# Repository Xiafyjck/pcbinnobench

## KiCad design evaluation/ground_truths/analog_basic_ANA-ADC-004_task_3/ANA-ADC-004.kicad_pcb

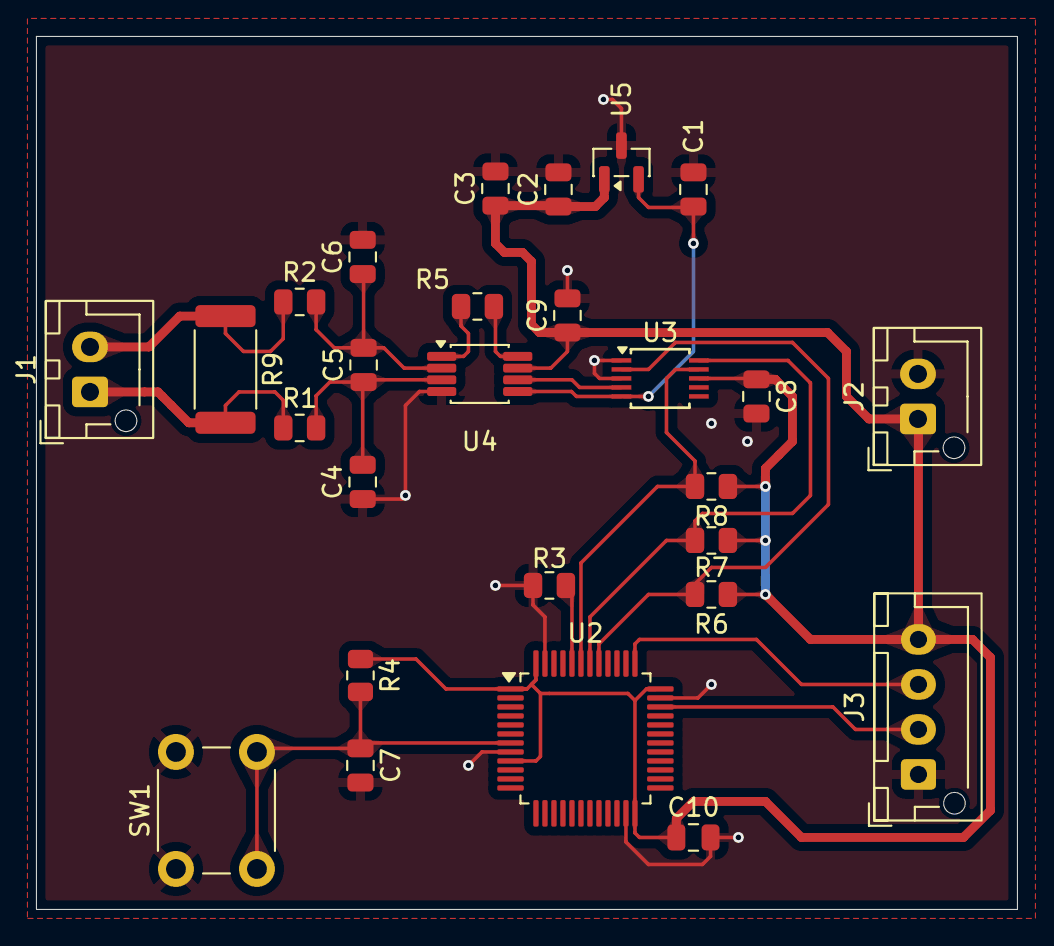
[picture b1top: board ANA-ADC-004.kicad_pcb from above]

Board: 2 copper layers, 54.5 x 48.5 mm, 27 parts (0 on the bottom side), 17 nets.

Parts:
C1: 10uF; C_0805_2012Metric
C2, C8, C9: 0.1uF; C_0805_2012Metric
C3: 1uF; C_0805_2012Metric
C4, C5, C6: 1nF; C_0805_2012Metric
C7, C10: 100nF; C_0805_2012Metric
J1, J2: Conn_01x02_Pin; JST_XH_B2B-XH-AM_1x02_P2.50mm_Vertical
J3: Conn_01x04_Pin; JST_XH_B4B-XH-AM_1x04_P2.50mm_Vertical
R1, R2, R3, R4, R6: 10k; R_0805_2012Metric
R5: 100k; R_0805_2012Metric
R7, R8: 4.7k; R_0805_2012Metric
R9: 10; R_2512_6332Metric
SW1: SW_Push; SW_PUSH_6mm
U2: STM32F103C8Tx; LQFP-48_7x7mm_P0.5mm
U3: ADS1115IDGS; TSSOP-10_3x3mm_P0.5mm
U4: INA333xxDGK; VSSOP-8_3x3mm_P0.65mm
U5: REF3012; SOT-23

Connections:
+3.3V: C2.1, C3.1, C8.1, C9.1, C10.1, J2.1, J3.4, R4.1, R6.1, R7.1, R8.1, U2.1 (VBAT), U2.9 (VDDA), U2.24 (VDD), U2.36 (VDD), U2.48 (VDD), U3.8 (VDD), U4.7 (V+), U5.1 (IN)
/ADC_HIN: J1.1, R1.1, R9.2
/ADC_LIN: J1.2, R2.1, R9.1
/stm32/ADS_ALERT: R6.2, U2.41 (PB5), U3.2 (ALERT/RDY)
/stm32/BOOT0: R3.1, U2.44 (BOOT0)
/stm32/I2C1_SCL: R7.2, U2.42 (PB6), U3.10 (SCL)
/stm32/I2C1_SDA: R8.2, U2.43 (PB7), U3.9 (SDA)
/stm32/NRST: C7.1, R4.2, SW1.2, U2.7 (NRST)
/stm32/swclk: J3.3, U2.37 (PA14)
/stm32/swdio: J3.2, U2.34 (PA13)
/vref: C1.1, U3.5 (AIN1), U4.5 (Ref), U5.2 (OUT)
GND: C1.2, C2.2, C3.2, C4.1, C6.2, C7.2, C8.2, C9.2, C10.2, J2.2, J3.1, R3.2, SW1.1, U2.8 (VSSA), U2.23 (VSS), U2.35 (VSS), U2.47 (VSS), U3.1 (ADDR), U3.3 (GND), U4.4 (V-), U5.3 (GND)
unnamed: R5.1, U4.8 (Rg)
unnamed: R5.2, U4.1 (Rg)
unnamed: U3.4 (AIN0), U4.6
unnamed: C4.2, C5.1, R1.2, U4.3 (+)
unnamed: C5.2, C6.1, R2.2, U4.2 (-)

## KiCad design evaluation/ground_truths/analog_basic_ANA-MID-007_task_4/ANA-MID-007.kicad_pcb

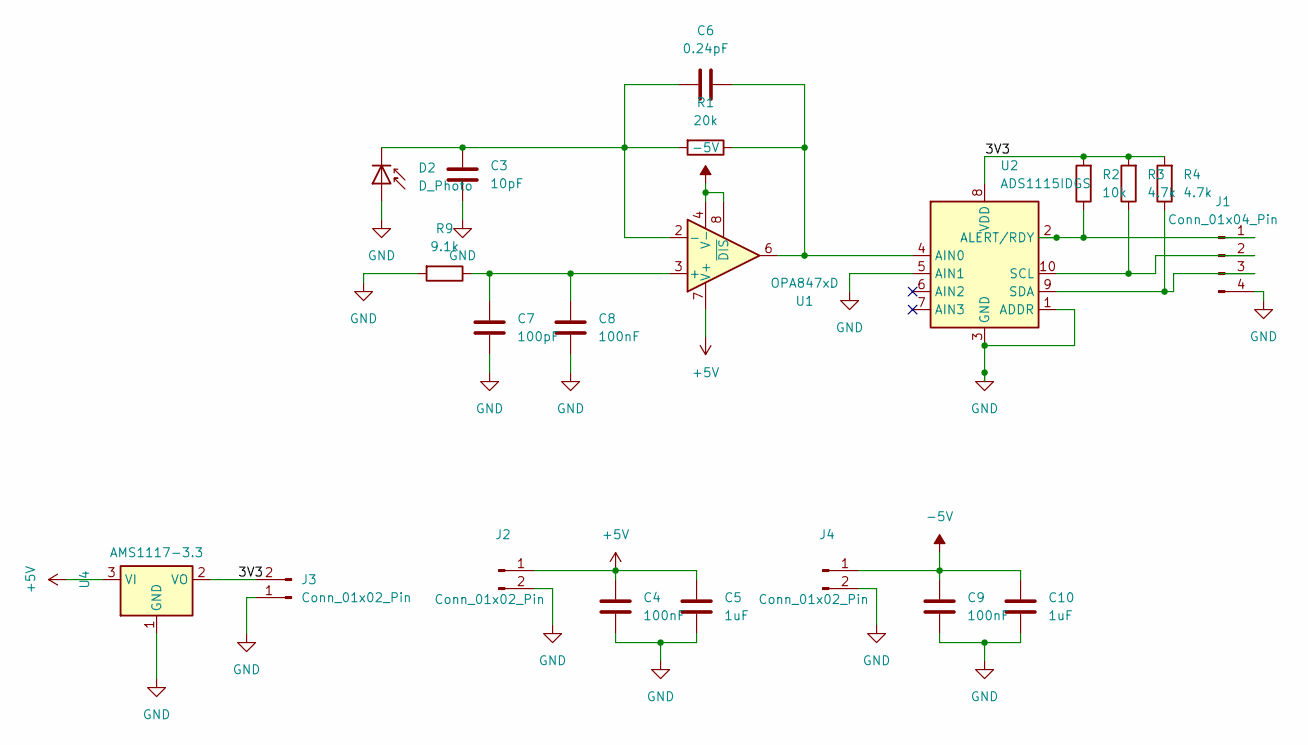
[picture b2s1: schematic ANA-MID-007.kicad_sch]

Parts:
C3: 10pF; C_0805_2012Metric
C4, C8, C9: 100nF; C_0805_2012Metric
C5, C10: 1uF; C_0805_2012Metric
C6: 0.24pF; C_0805_2012Metric
C7: 100pF; C_0805_2012Metric
D2: D_Photo; TO-18-2
J1: Conn_01x04_Pin; PinHeader_1x04_P2.54mm_Horizontal
J2, J3, J4: Conn_01x02_Pin; PinHeader_1x02_P2.54mm_Horizontal
R1: 20k; R_0805_2012Metric
R2: 10k; R_0805_2012Metric
R3, R4: 4.7k; R_0805_2012Metric
R9: 9.1k; R_0805_2012Metric
U1: OPA847xD; SOIC-8_3.9x4.9mm_P1.27mm
U2: ADS1115IDGS; TSSOP-10_3x3mm_P0.5mm
U4: AMS1117-3.3; SOT-223-3_TabPin2

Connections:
+5V: C4.1, C5.1, J2.1, U1.7 (V+), U4.3 (VI); also elsewhere on the board
-5V: C9.1, C10.1, J4.1, U1.4 (V-), U1.8 (~DIS)
/3V3: J3.2, R2.2, R3.2, R4.2, U2.8 (VDD), U4.2 (VO); also elsewhere on the board
GND: C3.2, C4.2, C5.2, C7.2, C8.2, C9.2, C10.2, D2.2 (A), J1.4, J2.2, J3.1, J4.2, R9.2, U2.1 (ADDR), U2.3 (GND), U2.5 (AIN1), U4.1 (GND); also elsewhere on the board
unnamed: C3.1, C6.1, D2.1 (K), R1.2, U1.2 (-)
unnamed: J1.1, R2.1, U2.2 (ALERT/RDY)
unnamed: J1.2, R3.1, U2.10 (SCL)
unnamed: J1.3, R4.1, U2.9 (SDA)
unnamed: C7.1, C8.1, R9.1, U1.3 (+)
unnamed: C6.2, R1.1, U1.6, U2.4 (AIN0)

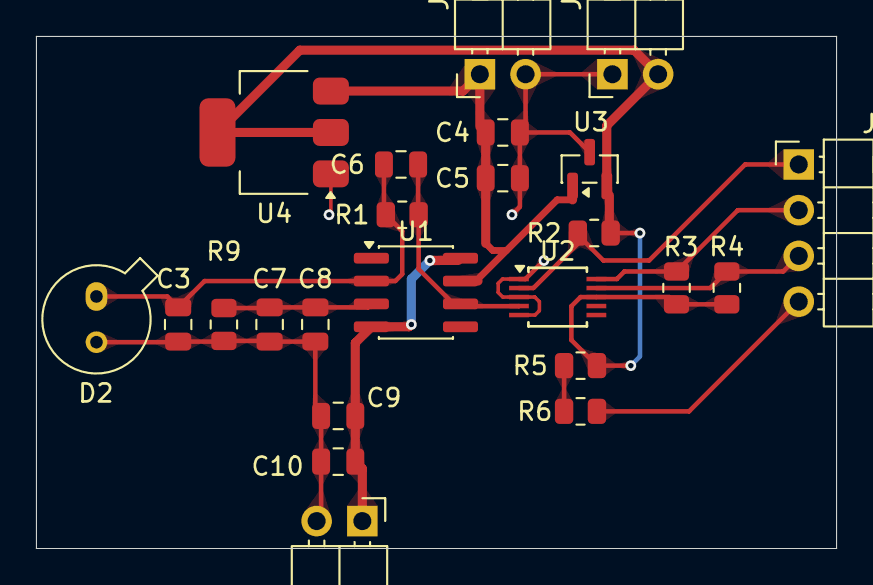
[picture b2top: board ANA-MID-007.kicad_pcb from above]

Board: 2 copper layers, 44.5 x 28.4 mm, 24 parts (0 on the bottom side), 11 nets.

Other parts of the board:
R5, R6: 10k; R_0805_2012Metric
U3: REF3033; SOT-23

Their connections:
+5V: U3.1 (IN); also elsewhere on the board
/3V3: R5.2, U3.2 (OUT); also elsewhere on the board
GND: R6.1, U3.3 (GND); also elsewhere on the board
unnamed: R5.1, R6.2

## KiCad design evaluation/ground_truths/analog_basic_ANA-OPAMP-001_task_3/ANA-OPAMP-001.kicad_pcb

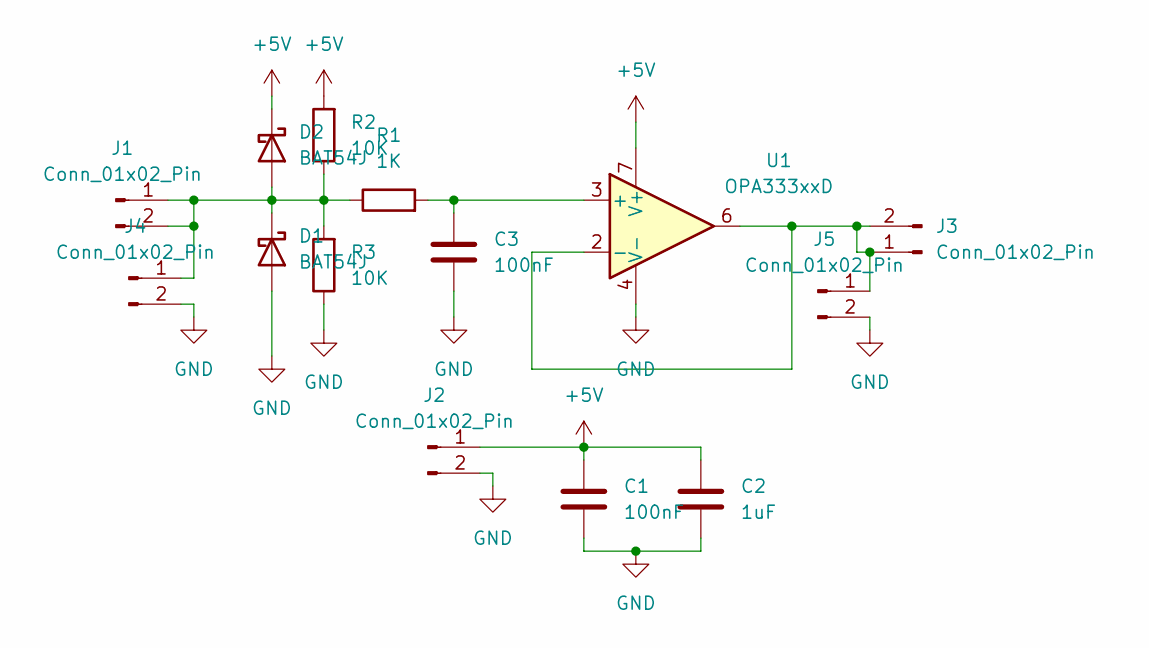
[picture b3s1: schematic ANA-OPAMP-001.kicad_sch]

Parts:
C1, C3: 100nF; C_0805_2012Metric
C2: 1uF; C_0805_2012Metric
D1, D2: BAT54J; D_SOD-323F
J1, J2, J3: Conn_01x02_Pin; PinHeader_1x02_P2.54mm_Horizontal
J4, J5: Conn_01x02_Pin; SMA_Amphenol_132289_EdgeMount
R1: 1K; R_0805_2012Metric
R2, R3: 10K; R_0805_2012Metric
U1: OPA333xxD; SOIC-8_3.9x4.9mm_P1.27mm

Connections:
+5V: C1.1, C2.1, D2.1 (K), J2.1, R2.2, U1.7 (V+)
GND: C1.2, C2.2, C3.2, D1.2 (A), J2.2, J4.2, J5.2, R3.1, U1.4 (V-)
unnamed: D1.1 (K), D2.2 (A), J1.1, J1.2, J4.1, R1.1, R2.1, R3.2
unnamed: J3.1, J3.2, J5.1, U1.2 (-), U1.6
unnamed: C3.1, R1.2, U1.3 (+)

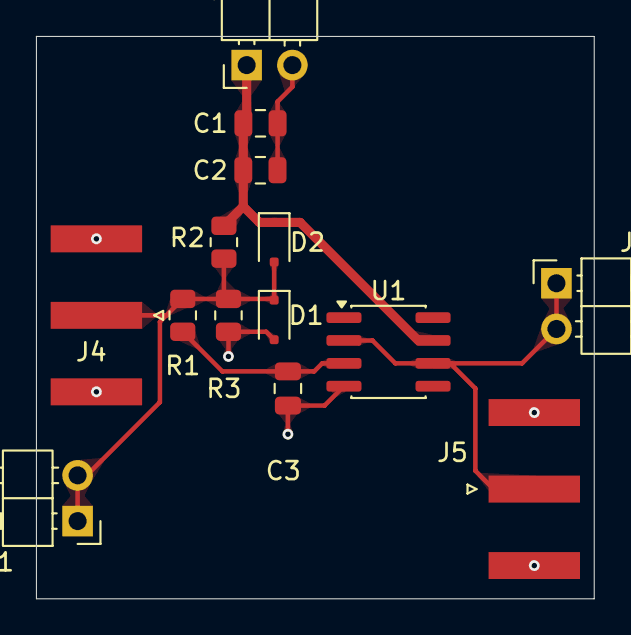
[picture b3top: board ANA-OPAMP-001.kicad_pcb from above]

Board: 2 copper layers, 31.0 x 31.2 mm, 14 parts (0 on the bottom side), 5 nets.

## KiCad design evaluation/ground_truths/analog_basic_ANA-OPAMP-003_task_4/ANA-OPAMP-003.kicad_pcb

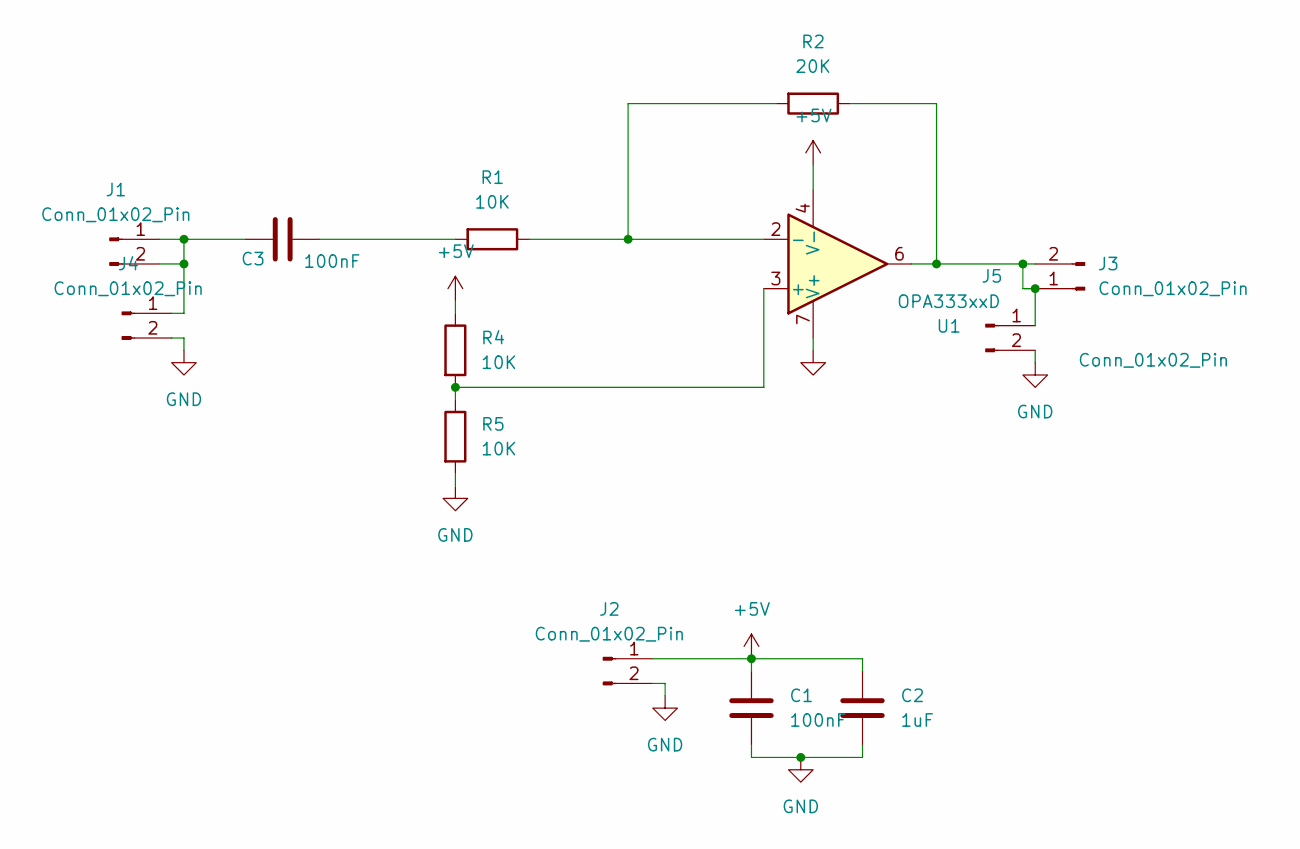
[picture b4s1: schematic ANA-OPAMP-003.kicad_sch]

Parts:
C1, C3: 100nF; C_0805_2012Metric
C2: 1uF; C_0805_2012Metric
J1, J2, J3: Conn_01x02_Pin; PinHeader_1x02_P2.54mm_Horizontal
J4, J5: Conn_01x02_Pin; SMA_Amphenol_132289_EdgeMount
R1, R4, R5: 10K; R_0805_2012Metric
R2: 20K; R_0805_2012Metric
U1: OPA333xxD; SOIC-8_3.9x4.9mm_P1.27mm

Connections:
+5V: C1.1, C2.1, J2.1, R4.1, U1.4 (V-)
GND: C1.2, C2.2, J2.2, J4.2, J5.2, R5.2, U1.7 (V+); also elsewhere on the board
unnamed: C3.2, R1.2
unnamed: C3.1, J1.1, J1.2, J4.1
unnamed: J3.1, J3.2, J5.1, R2.1, U1.6
unnamed 5: R4.2, R5.1, U1.3 (+); also elsewhere on the board
unnamed: R1.1, R2.2, U1.2 (-)

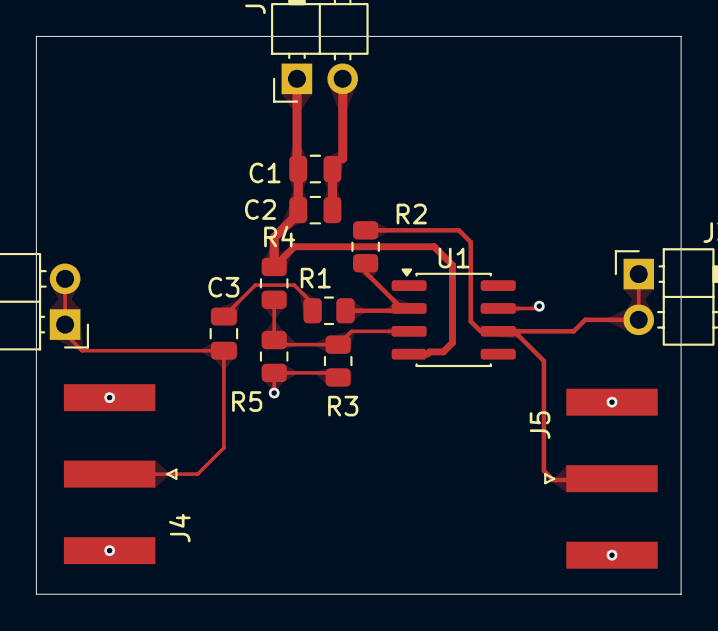
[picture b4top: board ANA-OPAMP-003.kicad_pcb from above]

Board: 2 copper layers, 35.8 x 31.0 mm, 14 parts (0 on the bottom side), 7 nets.

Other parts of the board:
R3: 1.5K; R_0805_2012Metric

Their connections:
GND: R3.2; also elsewhere on the board
unnamed 5: R3.1; also elsewhere on the board

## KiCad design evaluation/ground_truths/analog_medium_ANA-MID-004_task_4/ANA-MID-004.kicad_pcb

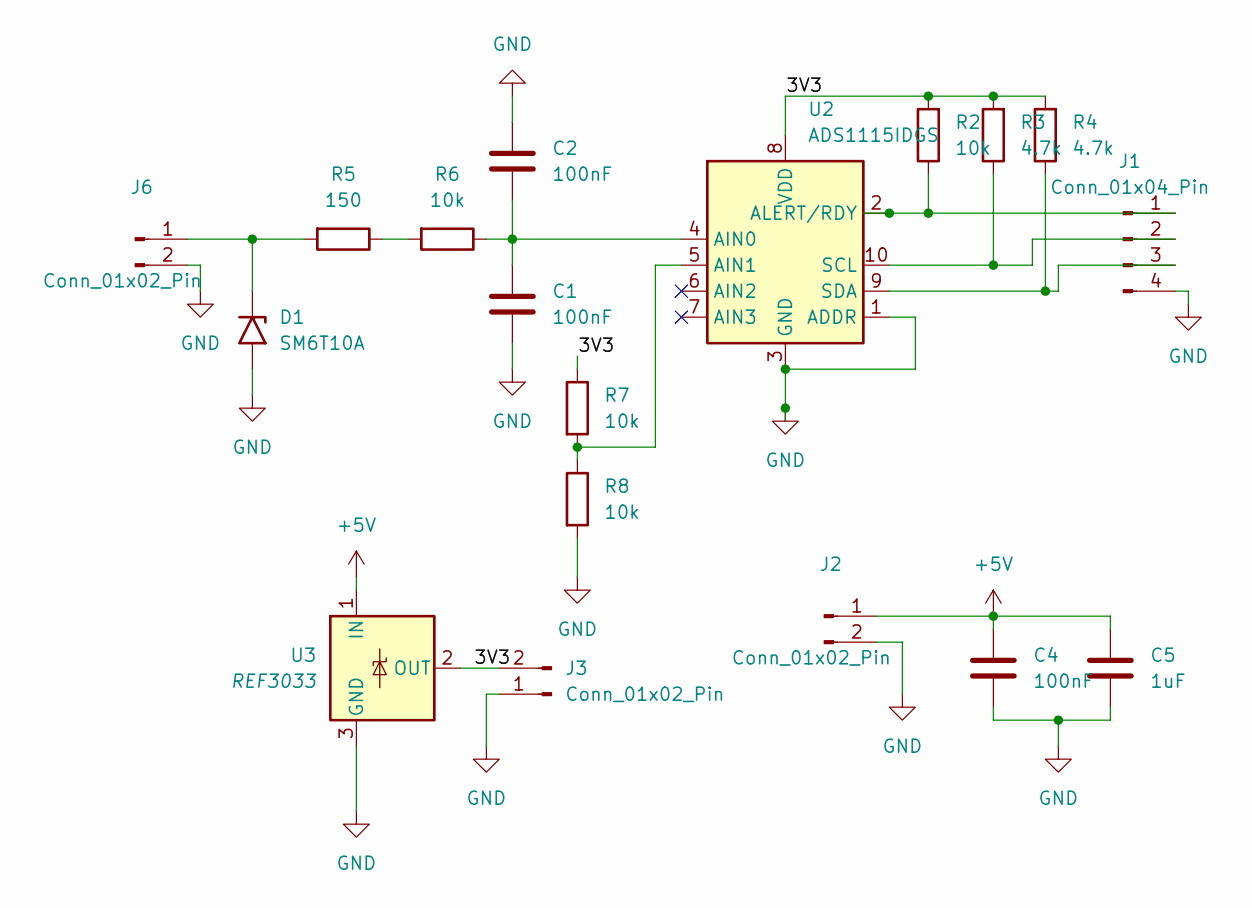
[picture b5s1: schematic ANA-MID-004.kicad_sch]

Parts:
C1, C2, C4: 100nF; C_0805_2012Metric
C5: 1uF; C_0805_2012Metric
D1: SM6T10A; D_SMB
J1: Conn_01x04_Pin; PinHeader_1x04_P2.54mm_Horizontal
J2, J3, J6: Conn_01x02_Pin; PinHeader_1x02_P2.54mm_Horizontal
R2, R6, R7, R8: 10k; R_0805_2012Metric
R3, R4: 4.7k; R_0805_2012Metric
R5: 150; R_1206_3216Metric
U2: ADS1115IDGS; TSSOP-10_3x3mm_P0.5mm
U3: REF3033; SOT-23

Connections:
+5V: C4.1, C5.1, J2.1, U3.1 (IN)
/3V3: J3.2, R2.2, R3.2, R4.2, R7.1, U2.8 (VDD), U3.2 (OUT)
GND: C1.2, C2.1, C4.2, C5.2, D1.2 (A2), J1.4, J2.2, J3.1, J6.2, R8.2, U2.1 (ADDR), U2.3 (GND), U3.3 (GND)
unnamed: D1.1 (A1), J6.1, R5.2
unnamed: J1.1, R2.1, U2.2 (ALERT/RDY)
unnamed: J1.2, R3.1, U2.10 (SCL)
unnamed: J1.3, R4.1, U2.9 (SDA)
unnamed: R5.1, R6.2
unnamed: C1.1, C2.2, R6.1, U2.4 (AIN0)
unnamed: R7.2, R8.1, U2.5 (AIN1)

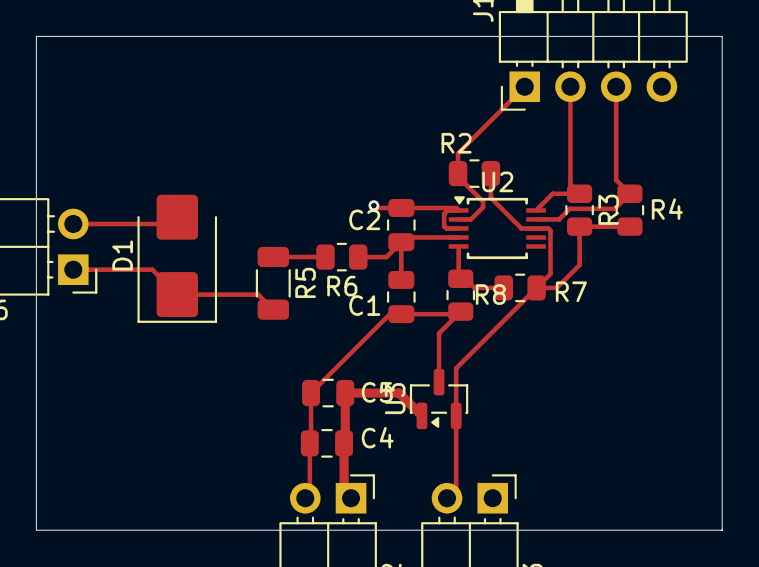
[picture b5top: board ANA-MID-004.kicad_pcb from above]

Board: 2 copper layers, 38.1 x 27.4 mm, 18 parts (0 on the bottom side), 10 nets.

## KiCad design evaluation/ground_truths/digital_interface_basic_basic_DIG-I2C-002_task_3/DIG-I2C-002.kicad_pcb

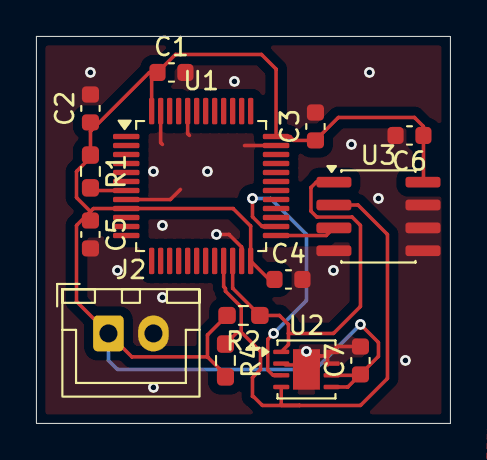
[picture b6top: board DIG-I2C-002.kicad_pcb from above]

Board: 2 copper layers, 23.0 x 21.5 mm, 14 parts (0 on the bottom side), 7 nets.

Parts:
C1, C2, C3, C4, C5, C6, C7: 100NF; C_0603_1608Metric
J2: Conn_01x02_Pin; JST_XH_B2B-XH-A_1x02_P2.50mm_Vertical
R1: 10K; R_0603_1608Metric_Pad0.98x0.95mm_HandSolder
R2, R4: 4.7K; R_0603_1608Metric_Pad0.98x0.95mm_HandSolder
U1: STM32F103C8Tx; LQFP-48_7x7mm_P0.5mm
U2: SHT30-DIS; DFN-8-1EP_3x3mm_P0.65mm_EP1.5x2.25mm
U3: LM75B; SOIC-8_3.9x4.9mm_P1.27mm

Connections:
+3V3: C1.1, C2.1, C3.1, C4.1, C5.1, C6.1, C7.1, J2.1, R1.1, R2.2, R4.2, U1.9 (VDDA), U1.24 (VDD), U1.36 (VDD), U1.48 (VDD), U2.5 (VDD), U2.6 (~RESET), U3.8 (+Vs)
/groundtruth1/ALERT: U1.26 (PB13), U2.3 (ALERT)
/groundtruth1/I2C_SCL: R4.1, U1.21 (PB10), U2.4 (SCL), U3.2 (SCL)
/groundtruth1/I2C_SDA: R2.1, U1.22 (PB11), U2.1 (SDA), U3.1 (SDA)
/groundtruth1/O.S: U1.25 (PB12), U3.3 (O.S.)
GND: C1.2, C2.2, C3.2, C4.2, C5.2, C6.2, C7.2, J2.2, U1.8 (VSSA), U1.23 (VSS), U1.35 (VSS), U1.44 (BOOT0), U1.47 (VSS), U2.2 (ADDR), U2.7 (R), U2.8 (VSS), U2.9 (VSS), U3.4 (GND), U3.5 (A2), U3.6 (A1), U3.7 (A0)
unnamed: R1.2, U1.7 (NRST)

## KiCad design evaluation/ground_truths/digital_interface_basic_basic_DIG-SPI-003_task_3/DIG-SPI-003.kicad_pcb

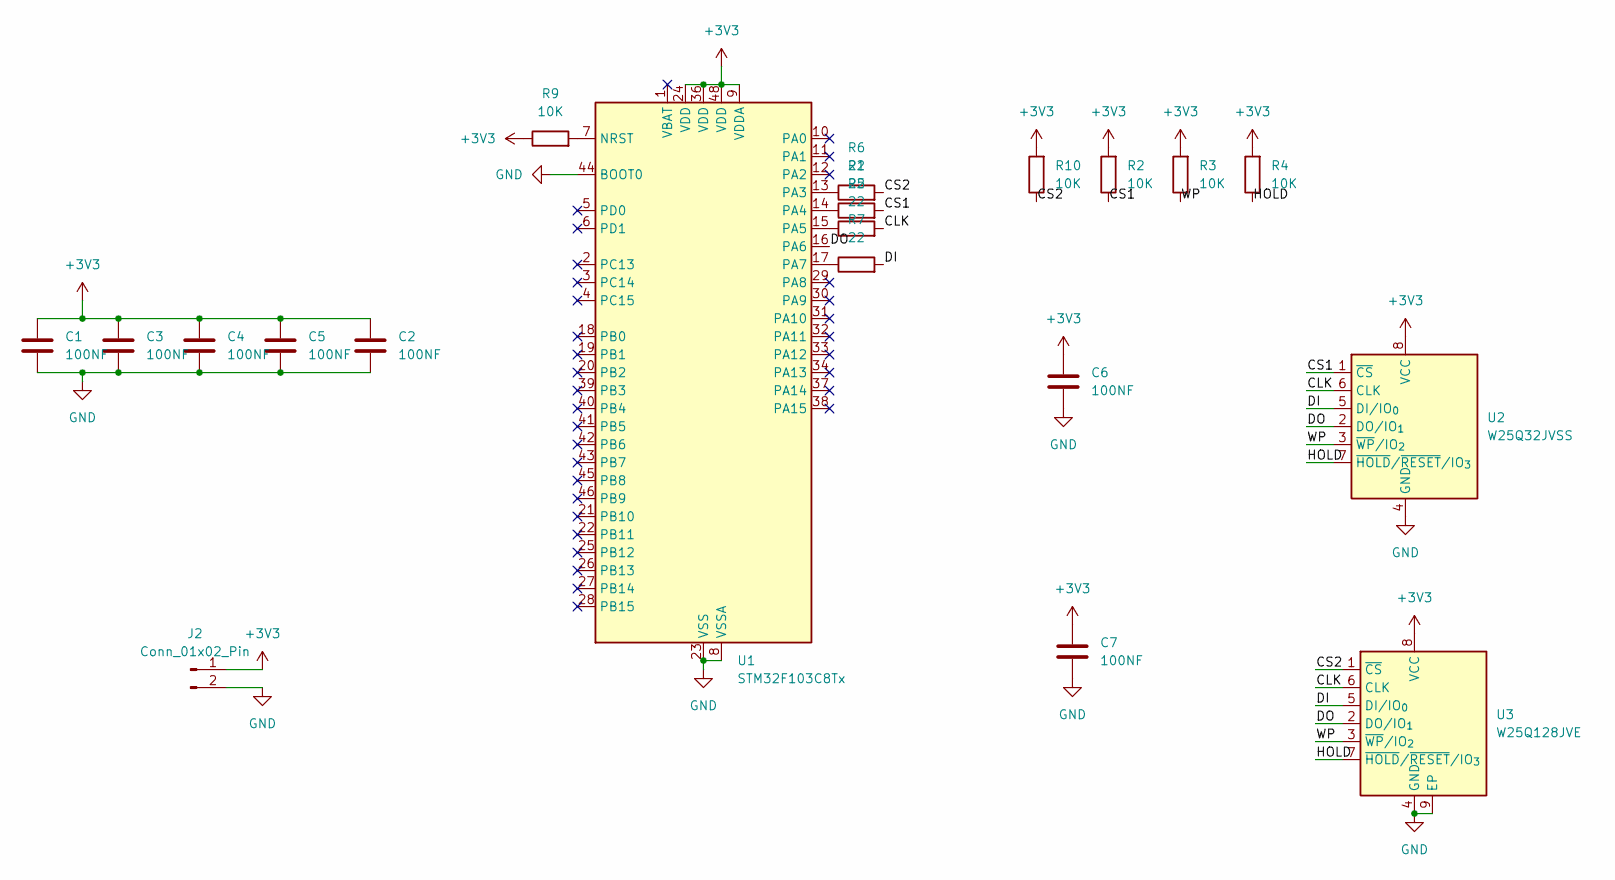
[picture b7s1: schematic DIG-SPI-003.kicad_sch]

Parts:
C1, C2, C3, C4, C5, C6, C7: 100NF; C_0603_1608Metric
J2: Conn_01x02_Pin; JST_XH_B2B-XH-A_1x02_P2.50mm_Vertical
R1, R5, R6, R7: 22; R_0201_0603Metric
R2, R3, R4, R9, R10: 10K; R_0603_1608Metric
U1: STM32F103C8Tx; LQFP-48_7x7mm_P0.5mm
U2: W25Q32JVSS; SOIC-8_5.3x5.3mm_P1.27mm
U3: W25Q128JVE; WSON-8-1EP_6x5mm_P1.27mm_EP3.4x4.3mm

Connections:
+3V3: C1.1, C2.1, C3.1, C4.1, C5.1, C6.1, C7.1, J2.1, R2.2, R3.2, R4.2, R9.1, R10.2, U1.9 (VDDA), U1.24 (VDD), U1.36 (VDD), U1.48 (VDD), U2.8 (VCC), U3.8 (VCC)
/CLK: R5.2, U2.6 (CLK), U3.6 (CLK)
/CS1: R1.2, R2.1, U2.1 (~CS)
/CS2: R6.2, R10.1, U3.1 (~CS)
/DI: R7.2, U2.5 (DI/IO_{0}), U3.5 (DI/IO_{0})
/DO: U1.16 (PA6), U2.2 (DO/IO_{1}), U3.2 (DO/IO_{1})
/HOLD: R4.1, U2.7 (~HOLD/~RESET/IO_{3}), U3.7 (~HOLD/~RESET/IO_{3})
/WP: R3.1, U2.3 (~WP/IO_{2}), U3.3 (~WP/IO_{2})
GND: C1.2, C2.2, C3.2, C4.2, C5.2, C6.2, C7.2, J2.2, U1.8 (VSSA), U1.23 (VSS), U1.35 (VSS), U1.44 (BOOT0), U1.47 (VSS), U2.4 (GND), U3.4 (GND), U3.9 (EP)
unnamed: R9.2, U1.7 (NRST)
unnamed: R6.1, U1.13 (PA3)
unnamed: R1.1, U1.14 (PA4)
unnamed: R5.1, U1.15 (PA5)
unnamed: R7.1, U1.17 (PA7)

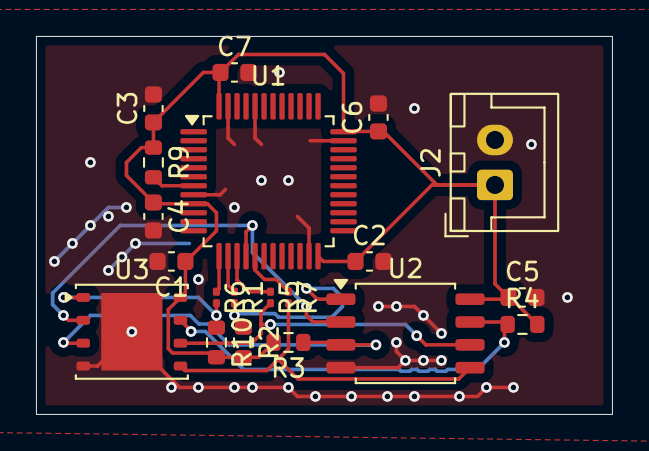
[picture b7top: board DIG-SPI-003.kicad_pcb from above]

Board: 2 copper layers, 32.0 x 21.0 mm, 20 parts (0 on the bottom side), 14 nets.
